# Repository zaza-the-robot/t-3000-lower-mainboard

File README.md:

# t-3000-lower-mainboard
The interface board between the upper and lower sides of the robot

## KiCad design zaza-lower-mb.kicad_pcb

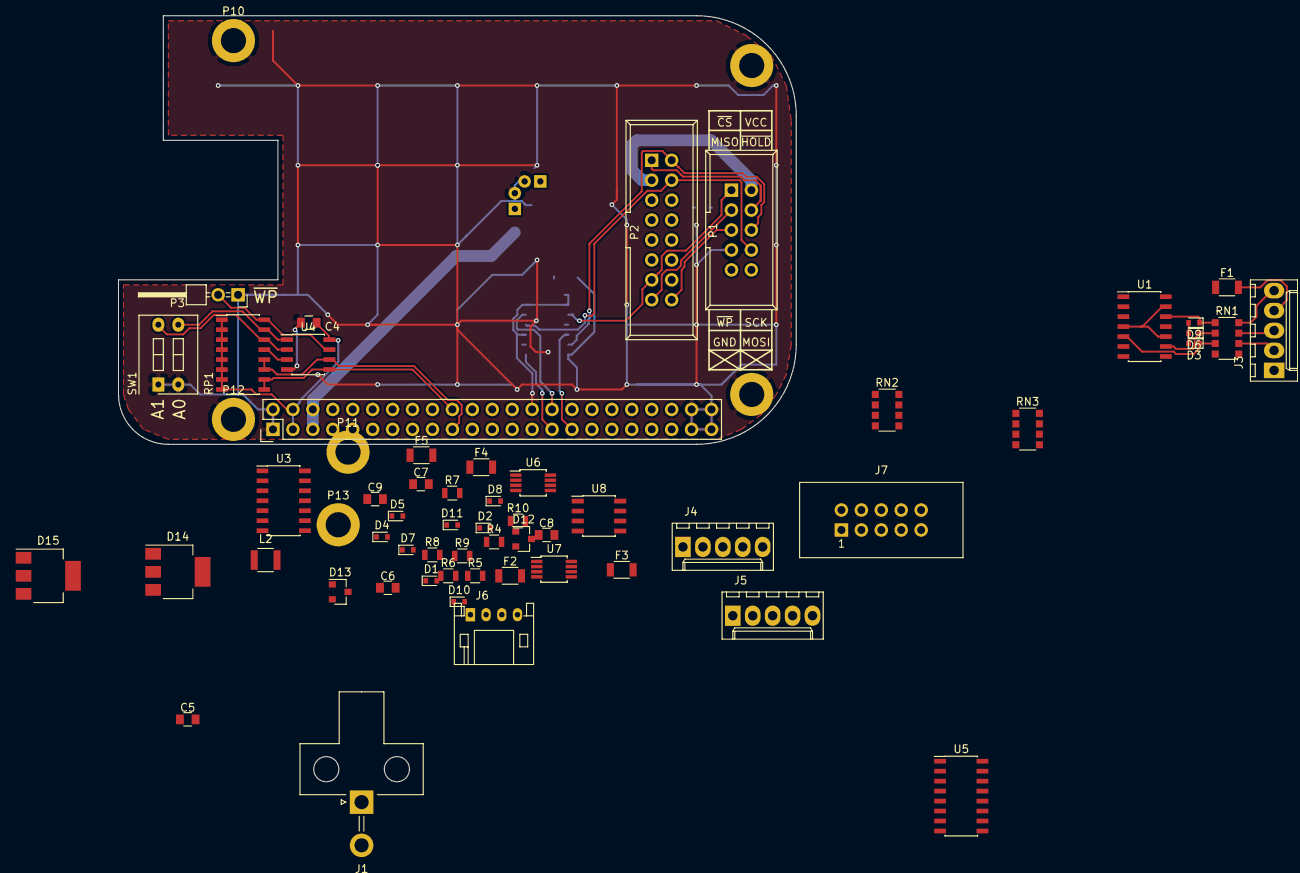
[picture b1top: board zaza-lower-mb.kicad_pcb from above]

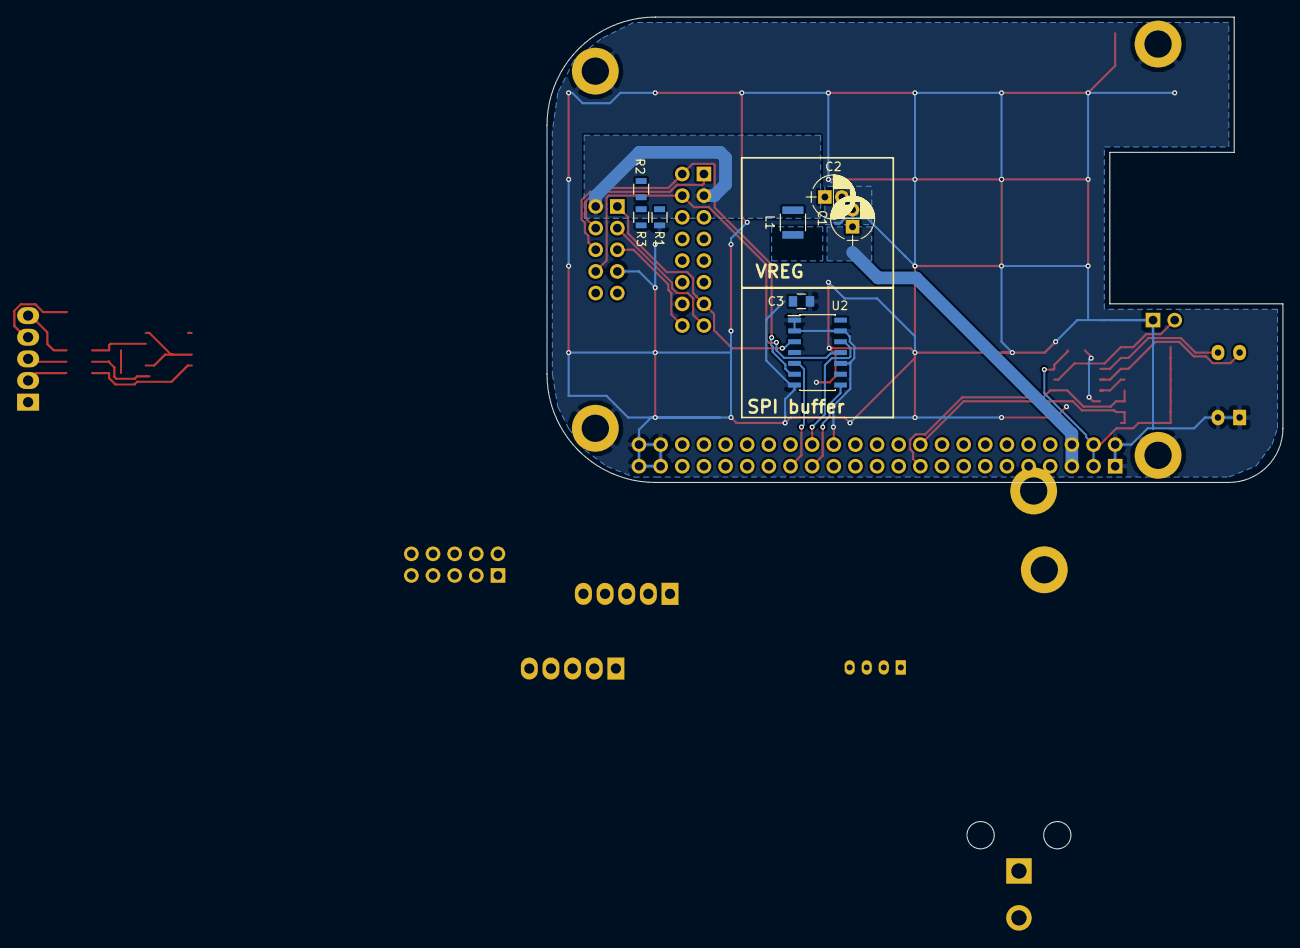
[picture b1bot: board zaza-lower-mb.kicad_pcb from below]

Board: 2 copper layers, 86.4 x 54.6 mm, 70 parts (8 on the bottom side), 60 nets.

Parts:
C1, C2: 1u; CP_Radial_D5.0mm_P2.00mm
C3, C5, C6, C7, C8, C9: 1u; C_0805
C4: 0.1uF; C_0805
D1, D2, D3, D4, D5, D6, D7, D8, D9, D10, D11: TVS; D_SOD-523
D12, D13: 6V; SOT-23
D14, D15: BT168; SOT-223-3Lead_TabPin2
F1, F2, F3: 50mA; R_1206
F4, F5: 500mA; R_1206
J1: BBPC; Molex_MiniFit-JR-5569-02A1_2x01x4.20mm_Angled
J3, J4, J5: KK 2.54; Molex_KK-6410-05_05x2.54mm_Straight
J6: JST 2.0mm; JST_PH_S4B-PH-K_04x2.00mm_Angled
J7: IDC-10; IDC_Header_Straight_10pins
L1, L2: 220N; L_1210
P1: SPI-8; IDC_Header_Straight_10pins
P2: SPI-16; IDC_Header_Straight_16pins
P3: EEPROM_PROG_EN; Pin_Header_Angled_2x01
P4: BBB_P9; Pin_Header_Straight_2x23
P8: BBB_P8; MountingHole_3.2mm_M3_ISO14580_Pad
P9: BBB_P9; MountingHole_3.2mm_M3_ISO14580_Pad
P10, P11, P12, P13: CONN_01X01; MountingHole_3.2mm_M3_ISO14580_Pad
R1, R2, R3, R4: 270k; R_0805
R5, R6, R7, R8, R9, R10: 4.7K; R_0805
RN1, RN2, RN3: R_Pack04; R_Array_Convex_4x1206
RP1: 10k; SOIC-16_3.9x9.9mm_Pitch1.27mm
SW1: DIPS_02; SW_DIP_x2_Slide
U1, U2, U3: 74LVC125; SOIC-14_3.9x8.7mm_Pitch1.27mm
U4: CAT24C256W; SOIC-8_3.9x4.9mm_Pitch1.27mm
U5: 74xx148; SOIC-16_3.9x9.9mm_Pitch1.27mm
U6, U7: LM5008MM; MSOP-8_3x3mm_Pitch0.65mm
U8: ISL83491; SOIC-8_3.9x4.9mm_Pitch1.27mm

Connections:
+3V3: C4.1, J7.1, P4.3, P4.4, RP1.1, RP1.2, RP1.3, RP1.4, RP1.5, RP1.6, RP1.7, RP1.8, U1.14, U2.14, U3.14, U4.8, U5.4, U5.5, U5.16
+5V: D12.1, D14.2, L1.2, P4.5, P4.6, R5.1
+5VP: D13.1, D15.2, F1.1, F2.1, F3.1, L2.2, R7.1
+48V: F4.2, F5.2, J1.1
/A0: RP1.15, SW1.3, U4.1
/A1: RP1.14, SW1.4, U4.2
/A2: RP1.13, U4.3
/CONN_MISO: P1.3, P2.15
/CONN_MOSI: P1.8, P2.4
/CONN_SCK: P1.6, P2.2
/DBG_RX: D1.1, J6.3
/DBG_TX: D2.1, J6.4
/ENC0_A: D6.1, RN1.2, U1.9
/ENC0_B: D9.1, RN1.1, U1.12
/ENC0_I: D3.1, RN1.3, U1.5
/ENC1_A: D7.1, RN2.2, U2.2
/ENC1_B: D10.1, RN2.1, U2.12
/ENC1_I: D4.1, RN2.3, U2.5
/ENC2_A: D8.1, RN3.2, U3.12
/ENC2_B: D11.1, RN3.1, U3.9
/ENC2_I: D5.1, RN3.3, U3.2
/I2C2_SCL: P4.19, RP1.11, RP1.12, U4.6
/I2C2_SDA: P4.20, RP1.9, RP1.10, U4.5
/~CONN_CS: P1.1, P2.13
/~CONN_HOLD: P1.4, P2.1
/~CONN_WP: P1.5, P2.16
/~WP: P3.2, RP1.16, U4.7
GND: C1.2, C2.2, C3.1, C4.2, C6.1, C8.2, C9.2, D1.2, D2.2, D3.2, D4.2, D5.2, D6.2, D7.2, D8.2, D9.2, D10.2, D11.2, D14.1, D15.1, J1.2, J3.1, J4.1, J5.1, J6.1, J7.7, P1.7, P2.14, P3.1, P4.1, P4.2, P4.43, P4.44, P4.45, P4.46, P8.1, P9.1, P10.1, P11.1, P12.1, P13.1, R1.2, R2.2, R6.2, R8.2, R9.2, R10.2, SW1.1, SW1.2, U1.4, U1.7, U1.10, U1.13, U2.1, U2.4, U2.7, U2.13, U3.1, U3.7, U3.10, U3.13, U4.4, U5.8, U6.4, U7.4, U8.6, U8.7
unnamed: C1.1, F4.1, R3.1, U6.8
unnamed: C2.1, F5.1, R4.1, U7.8
unnamed: C3.2, U6.7
unnamed: C5.1, U6.2
unnamed: C5.2, L1.1, U6.1
unnamed: C6.2, U7.7
unnamed: C7.1, U7.2
unnamed: C7.2, L2.1, U7.1
unnamed: C8.1, D12.2, D14.3, R9.1
unnamed: C9.1, D13.2, D15.3, R10.1
unnamed: F1.2, J3.4
unnamed: F2.2, J4.4
unnamed: F3.2, J5.4
unnamed: J3.2, RN1.6
unnamed: J3.3, RN1.7
unnamed: J3.5, RN1.8
unnamed: J4.2, RN2.6
unnamed: J4.3, RN2.7
unnamed: J4.5, RN2.8
unnamed: J5.2, RN3.6
unnamed: J5.3, RN3.7
unnamed: J5.5, RN3.8
unnamed: J7.8, U5.9
unnamed: J7.9, U5.7
unnamed: J7.10, U5.6
unnamed: R1.1, U6.3
unnamed: R2.1, U7.3
unnamed: R3.2, U6.6
unnamed: R4.2, U7.6
unnamed: R5.2, R6.1, U6.5
unnamed: R7.2, R8.1, U7.5
VCC: P1.2, P2.3

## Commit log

2017-11-05 schem
